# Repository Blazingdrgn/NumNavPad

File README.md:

# NumNavPad
My first PCB that I have made and it is compatible with the pro-micro and elite-c. 
It is a macropad that consists of the numpad and the navigation cluster. 
The numpad is inverted so it is meant to be used on the left side of the keyboard.

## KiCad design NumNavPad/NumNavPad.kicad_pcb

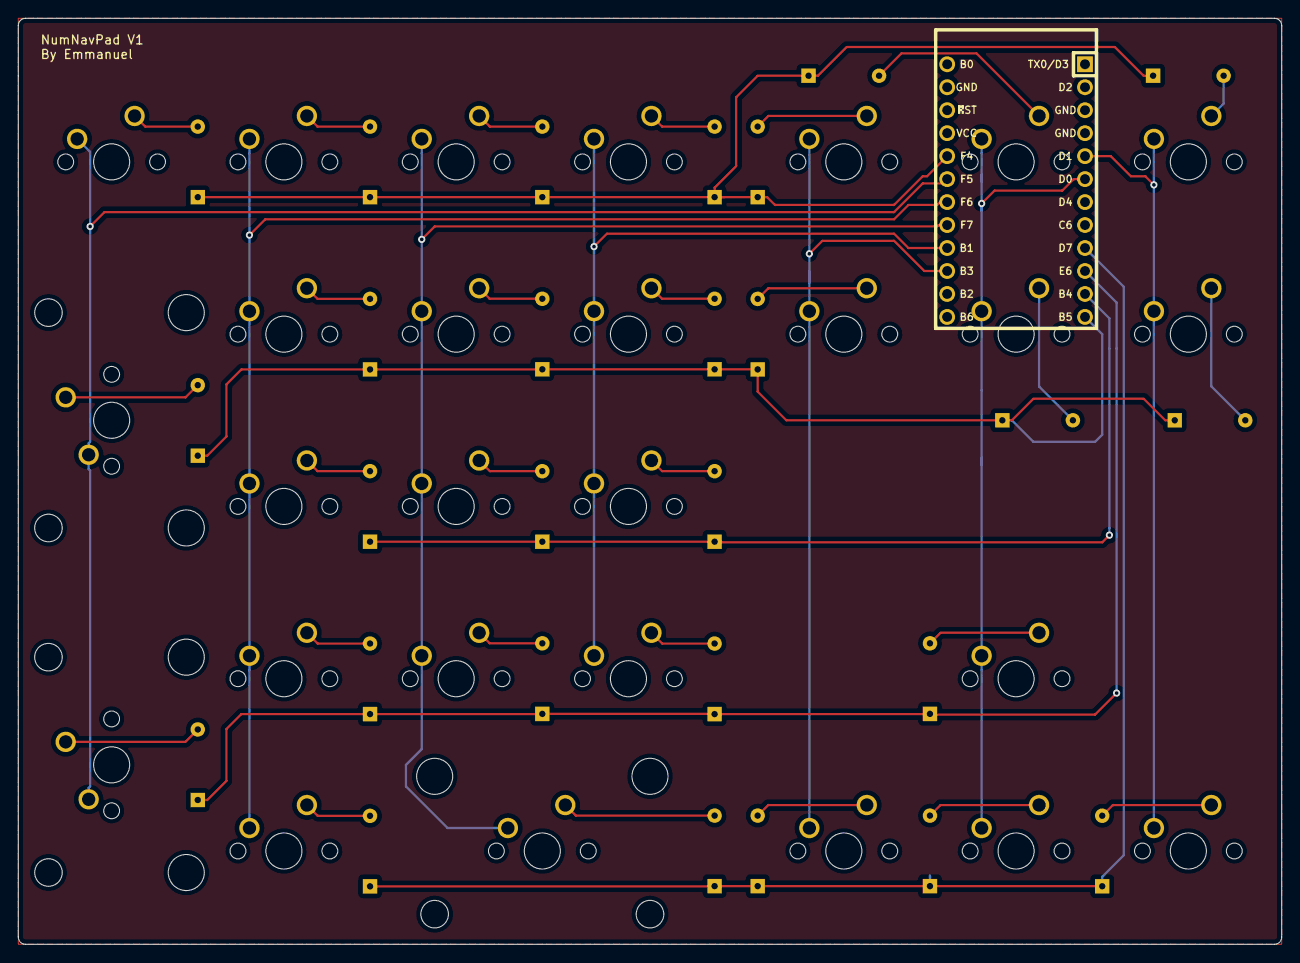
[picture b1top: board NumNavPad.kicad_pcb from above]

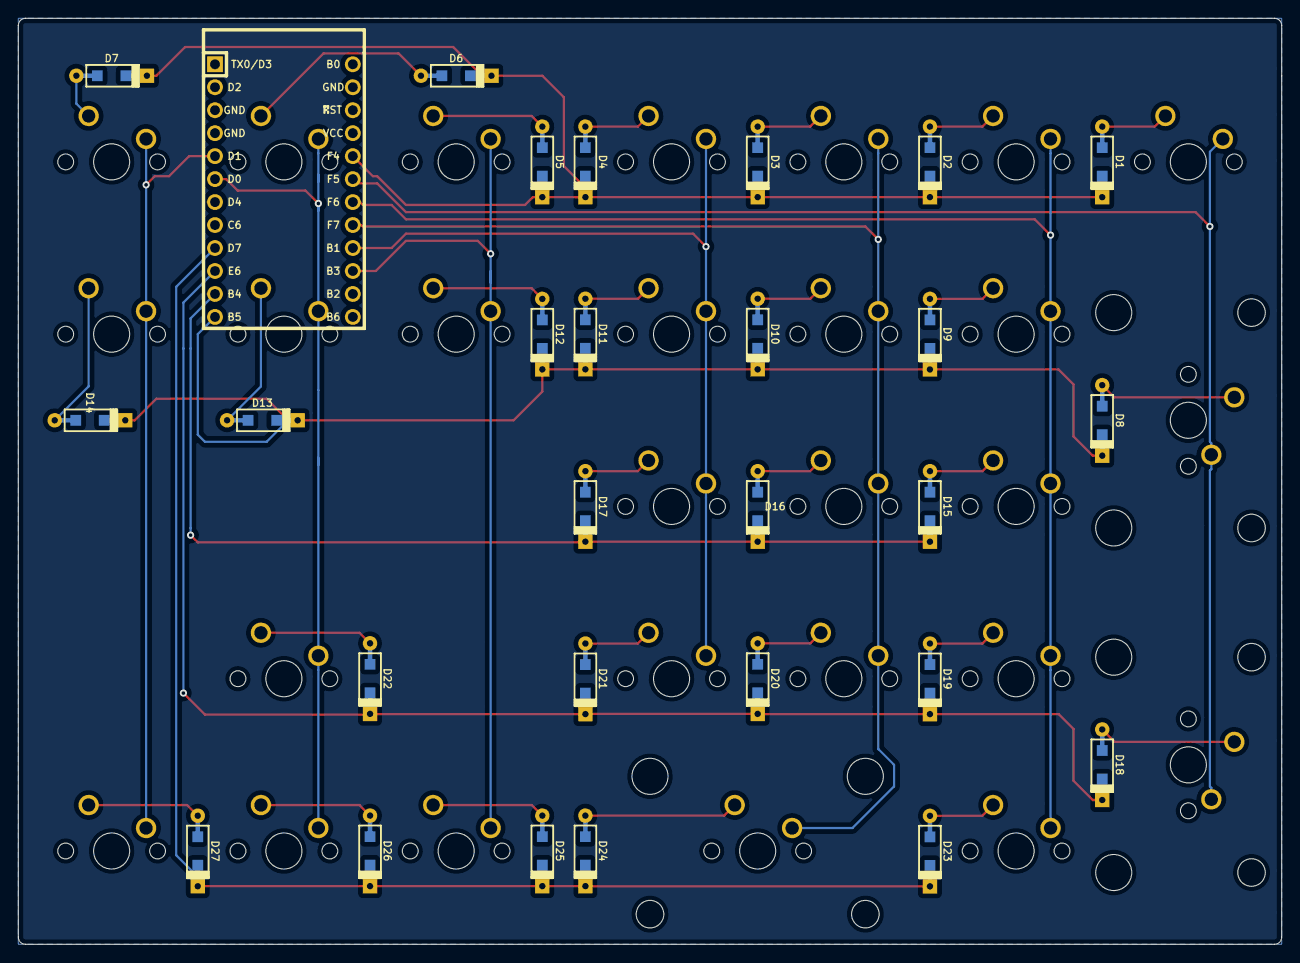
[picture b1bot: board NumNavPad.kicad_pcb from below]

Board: 2 copper layers, 139.7 x 102.4 mm, 55 parts (28 on the bottom side), 39 nets.

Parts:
D1, D2, D3, D4, D5, D6, D7, D8, D9, D10, D11, D12, D13, D14, D15, D16, D17, D18, D19, D20, D21, D22, D23, D24, D25, D26, D27: D_Small; D_SOD123_axial
MX1, MX2, MX3, MX4, MX5, MX6, MX7, MX9, MX10, MX11, MX12, MX13, MX14, MX15, MX16, MX17, MX19, MX20, MX21, MX22, MX23, MX25, MX26, MX27: MX-NoLED; MXOnly-1U-NoLED
MX8, MX18: MX-NoLED; MXOnly-2U-NoLED
MX24: MX-NoLED; MXOnly-2U-ReversedStabilizers-NoLED
U1: Elite-C; Elite-C-castellated-24pin-holes

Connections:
Col0: MX1.1, MX8.1, MX18.1, U1.19
Col1: MX2.1, MX9.1, MX15.1, MX19.1, MX23.1, U1.18
Col2: MX3.1, MX10.1, MX16.1, MX20.1, MX24.1, U1.17
Col3: MX4.1, MX11.1, MX17.1, MX21.1, U1.16
Col4: MX5.1, MX12.1, MX25.1, U1.15
Col5: MX6.1, MX13.1, MX22.1, MX26.1, U1.6
Col6: MX7.1, MX14.1, MX27.1, U1.5
unnamed: D1.2, MX1.2
unnamed: D2.2, MX2.2
unnamed: D3.2, MX3.2
unnamed: D4.2, MX4.2
unnamed: D5.2, MX5.2
unnamed: D6.2, MX6.2
unnamed: D7.2, MX7.2
unnamed: D8.2, MX8.2
unnamed: D9.2, MX9.2
unnamed: D10.2, MX10.2
unnamed: D11.2, MX11.2
unnamed: D12.2, MX12.2
unnamed: D13.2, MX13.2
unnamed: D14.2, MX14.2
unnamed: D15.2, MX15.2
unnamed: D16.2, MX16.2
unnamed: D17.2, MX17.2
unnamed: D18.2, MX18.2
unnamed: D19.2, MX19.2
unnamed: D20.2, MX20.2
unnamed: D21.2, MX21.2
unnamed: D22.2, MX22.2
unnamed: D23.2, MX23.2
unnamed: D24.2, MX24.2
unnamed: D25.2, MX25.2
unnamed: D26.2, MX26.2
unnamed: D27.2, MX27.2
Row0: D1.1, D2.1, D3.1, D4.1, D5.1, D6.1, D7.1, U1.20
Row1: D8.1, D9.1, D10.1, D11.1, D12.1, D13.1, D14.1, U1.12
Row2: D15.1, D16.1, D17.1, U1.11
Row3: D18.1, D19.1, D20.1, D21.1, D22.1, U1.10
Row4: D23.1, D24.1, D25.1, D26.1, D27.1, U1.9

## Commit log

2020-10-05 Initialize Project
2020-10-05 Adding Repos
2020-10-05 Revert "Adding Repos"
    This reverts commit be87426ba5030ba396ba3b01fb1fc65655a4f72c.
2020-10-05 Repos
2020-10-05 Add submodules
2020-10-05 Add Footprint libraries
2020-10-05 Schematic
2020-10-08 Schematic and Pcb finished
2020-10-08 Gerbers Added
